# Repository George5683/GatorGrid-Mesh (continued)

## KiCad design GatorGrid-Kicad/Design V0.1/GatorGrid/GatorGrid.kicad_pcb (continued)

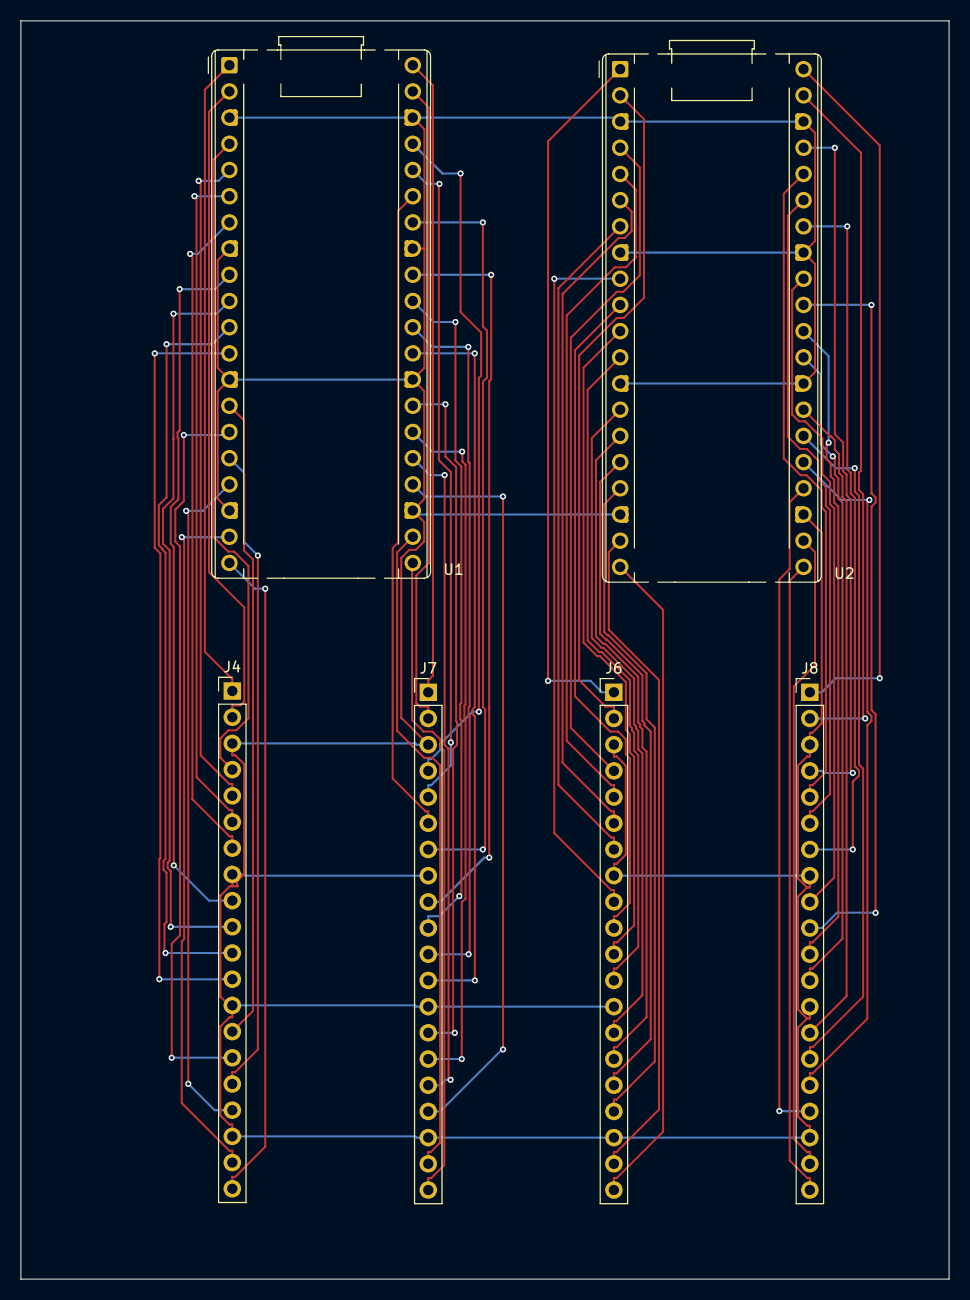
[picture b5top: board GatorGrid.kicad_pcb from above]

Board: 2 copper layers, 90.0 x 122.0 mm, 6 parts (0 on the bottom side), 65 nets.

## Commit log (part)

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2025-03-01 Working on the coding
2025-03-01 working on the coding...
2025-03-05 Fixed structure of project
2025-03-06 Restructured the code to have better functionality
2025-03-06 Restructured the code more
2025-03-06 added a comment
2025-03-06 removed testing commands
2025-03-07 Added STANode with scanning for other nodes *untested*
2025-03-07 Made multi-core polling and CMake for STA node testing
2025-03-10 converted the ap mode to have an enable/disable option for webpage generation
2025-03-10 implements doxygen with html
2025-03-11 testing...
2025-03-11 testing
2025-03-11 Add in the tcp client/server lib
2025-03-11 sta callback fix
2025-03-11 refactoring code and and added STANode tcp setup
2025-03-12 added tcp join message on init
2025-03-13 Add necessary TCP test functions to STA and AP libaries
2025-03-13 Fixed AP node TCP server test initalization
2025-03-13 refactor sta and ap mode setups to pull apart init code so they can be set up seperately themselves
2025-03-13 stash tcp branch
2025-03-13 Remove code that handles connection termination, also allows multiple clients to connect
2025-03-13 tcp client debugging
2025-03-13 Implements two way SPI communication
2025-03-13 working data transmission
2025-03-14 adding example files
2025-03-17 addded functionality
2025-03-19 Fixed memory leak issues and added sending a message for STA and receiving for AP
2025-03-23 updated README's
2025-03-25 Integrate Monocypher into code base
2025-03-27 Added picoNodeVectorClass
2025-04-01 Added a response back from AP whenever it gets a message
2025-04-01 Added messaging packets, INIT and DATA
2025-04-01 sets up automatic github pages workflow for doxygen
2025-04-01 Initial gh-pages commit
2025-04-01 Deploying to gh-pages from @ George5683/GatorGrid-Mesh@9408bfd56aad9ebf4bb832339b5d144ec4e8de41 🚀
2025-04-01 testing edits
2025-04-03 ACK messages
2025-04-03 updates index.html page for doxygen
2025-04-03 testing changes
2025-04-03 undo AP node accidental regression
2025-04-03 connection tracking vector
2025-04-03 Deploying to gh-pages from @ George5683/GatorGrid-Mesh@af39291f74b6d0666d905e82c10850361384b24b 🚀
2025-04-04 messages library and test TCP stream handling protocol
2025-04-05 unify RNGs
2025-04-07 Added sta functions and corresponding AP setup
2025-04-07 Updated APNode responding to incoming messages
2025-04-08 message recv methods
2025-04-08 fix AP control logic for parsing first message
2025-04-08 small fixes
2025-04-08 Add message storing Ring Buffer
2025-04-08 added a delay in Master SPI to wait for the Slave to initialize
2025-04-08 Integrate ring buffer into mesh node
2025-04-08 Rework server loop framework for AP node, now the main loop has been pulled outside of server specific functions
2025-04-08 Fix ring buffer
2025-04-08 Deploying to gh-pages from @ George5683/GatorGrid-Mesh@0fd86eadc9164e9a8be14ad41aa431bcd3f0da28 🚀
2025-04-08 fixing connection issues
2025-04-08 working connection
2025-04-08 tiny fixes
2025-04-08 Working yippee
2025-04-09 add src and dest to ring buffer, add ring buff digest logic to main
2025-04-09 Fix TCP packet buffering issue when doing message transfers
2025-04-09 Deploying to gh-pages from @ George5683/GatorGrid-Mesh@8590bb2787558b4fb964fe81840b6301445097a4 🚀
2025-04-09 added SPI to MESHNODE
2025-04-09 Deploying to gh-pages from @ George5683/GatorGrid-Mesh@9e40fa7865f5ab1c4f912dc9631bc267d9ae0b1f 🚀
2025-04-09 Changes to try to get everything to compile
2025-04-09 Testing merge between AP/STA and SPI
2025-04-09 Deploying to gh-pages from @ George5683/GatorGrid-Mesh@ebe74fe17888b8dbb08e9b242e9e568ddd66f5bc 🚀
2025-04-09 Deploying to gh-pages from @ George5683/GatorGrid-Mesh@3b9e1cfd1249049987f9cdc25aba9724e7d184a9 🚀
2025-04-09 STA Takes AP Node ID
2025-04-09 fixed bug for SPI sending ID
2025-04-09 Fix AP node crashing
2025-04-10 fixed pragma in source file
2025-04-10 Deploying to gh-pages from @ George5683/GatorGrid-Mesh@90d0fb41c1bd2f010006ecfe91de5703d05e04ad 🚀
2025-04-10 fixed ring buffer :)
2025-04-15 adds dht sensor library
2025-04-15 Creating tree for tracking nodes
2025-04-15 Update header
2025-04-17 spi and meshnode docs updated
2025-04-17 Deploying to gh-pages from @ George5683/GatorGrid-Mesh@56b9e9430297e3f74e8047001cf9007baed19d82 🚀
2025-04-17 spi docs
2025-04-17 Implementing inital tree for AP node
2025-04-17 Design update
2025-04-17 Deploying to gh-pages from @ George5683/GatorGrid-Mesh@2c9891114300862a98f139ec7ba850d3d9ad5e5b 🚀
2025-04-17 Deploying to gh-pages from @ George5683/GatorGrid-Mesh@6d5549e240390ef6749891b45eb29f188ea94038 🚀
2025-04-17 Deploying to gh-pages from @ George5683/GatorGrid-Mesh@1188b57ffe1db28e062e314415c503c34b555ade 🚀
2025-04-17 Deploying to gh-pages from @ George5683/GatorGrid-Mesh@081e60efe6d0598f2a8e630e937cc6f15b025ca3 🚀
2025-04-17 cpp file docs support
2025-04-17 fixed connection issues
2025-04-17 Deploying to gh-pages from @ George5683/GatorGrid-Mesh@b6e65119c27ab90f88d076bb01624436f59600d4 🚀
2025-04-17 updates spi docs
2025-04-17 comment out tree stuff, add more functionality for node id broadcasting
2025-04-17 Deploying to gh-pages from @ George5683/GatorGrid-Mesh@1f27188fee09cd10e11d067534907ece6cfc30a2 🚀
2025-04-17 sta fixes
2025-04-17 fix merge issue
2025-04-17 Deploying to gh-pages from @ George5683/GatorGrid-Mesh@30f25b66aed03688fc2cee9de35827c2699bc10d 🚀
2025-04-17 Deploying to gh-pages from @ George5683/GatorGrid-Mesh@1254ea3ee5fa6b1ab8e517cbe5d74b039ae0385c 🚀
2025-04-17 MPU Sensor Stuff
2025-04-17 Deploying to gh-pages from @ George5683/GatorGrid-Mesh@9b93db1a23dffa90aa3b0fb43b6147dcd9c644bb 🚀
2025-04-17 Deploying to gh-pages from @ George5683/GatorGrid-Mesh@03399c561fd94a97318b7014df2a12db13b2141b 🚀
2025-04-17 Update Doxyfile
2025-04-17 working doxygen
2025-04-17 ack message handling
2025-04-17 add get child count for update msg
2025-04-17 override bug fix
2025-04-17 comment out update message sending
2025-04-17 add voalitile
2025-04-17 hahahahahahha
2025-04-17 fixing ACK waiting
2025-04-17 added errors for NAK msg
2025-04-17 add extra nodes
2025-04-17 fix node 2
2025-04-17 ACK passing
2025-04-17 testing demo nodes
2025-04-17 make connect to root node
2025-04-18 refined Kicad
2025-04-18 add imu
2025-04-18 fixing
2025-04-18 most recent version
2025-04-18 meme
2025-04-18 Fix potential buffer wrap around issue
2025-04-18 AP fix rollback
2025-04-18 STA working sending message single way through root
2025-04-18 Fixes to Meshnode STA to ensure that it doesn't hang on one way message transfers
2025-04-18 Fixes for root
2025-04-21 Updated Readme instructions for DOxygen
2025-04-21 Unified STA send_data
2025-04-21 :facepalm:
2025-04-21 Mesh node send data
2025-04-22 doxy deploy
2025-04-22 Deploying to gh-pages from @ George5683/GatorGrid-Mesh@e9dace8dd1dc84a85a923d63efcd156fb2b5c584 🚀
2025-04-22 demo time
2025-04-22 Deploying to gh-pages from @ George5683/GatorGrid-Mesh@c808830c7483f19a16e4caf8c3fb4dd0ef240578 🚀
2025-04-25 fixing errors
2025-08-04 added files for voltage booster
2025-08-13 updated the schematic to have no errors on the error check
2025-08-21 updated PCB
2025-08-27 added V2
2025-08-28 Updated power management, channel usage and wpa protection for consistency testing
2025-08-28 Updating Kicad
2025-08-28 added cmake for SPI testing
2025-08-29 Added wire tests
2025-08-29 Updated SPI
2025-09-02 fixed connections
2025-09-04 Minor changes to schematic
2025-09-04 Update MeshNodeAP.cpp for new SPI
2025-09-04 Update MeshNodeSTA.cpp for SPI
2025-09-04 Update MeshNode.hpp to include SPI stuff
2025-09-04 updating the bugs
    Removed mention of SPI delay in README.
2025-09-04 Added test_tree files
2025-09-11 Create SerialMessages
2025-09-16 handling serial msgs
2025-09-16 Added UART Library :D
2025-09-16 Working commit
2025-09-17 added children tree get chidren and reverted CMakeLists
2025-09-17 added doxygen comments to APNode functions
2025-09-17 fixing KICAD
2025-09-18 reworked cmakelists, you are welcome lol
2025-09-18 cleaned up header and removed unused variables
2025-09-18 removed dynamic allocation from parseMessage
2025-09-18 Hype tree stuff with aura and hype moments
2025-09-18 Update MeshNodeAP.cpp
    set power mode to performance rather then defualt
2025-09-18 Update MeshNodeSTA.cpp
    fix connection issue for STA
2025-09-23 adding a Version 3.0
2025-09-23 Added Kicad to the readme features section
2025-09-23 Fixing Readme's
2025-09-24 working on it
2025-09-25 flushing out send_msg
2025-09-25 Added RSSI testing hype moment
2025-09-25 Completely removed parseMessage and dynamic allocation
2025-09-25 AP inter-node message handling *needs testing*
2025-09-26 Finalized V3.0
2025-09-30 unification work
2025-10-01 Cole unified (#21)
    * unify uart
    * unification work
2025-10-01 Ggm 1 (#18)
    * cleaned up header and removed unused variables
    * removed dynamic allocation from parseMessage
    * flushing out send_msg
    * Completely removed parseMessage and dynamic allocation
    * AP inter-node message handling *needs testing*
    * fixed find_path_parent and split STANodes files
2025-10-01 removed commented out code
2025-10-01 tested serial and updating tree fixes
2025-10-01 Finished V3
2025-10-01 Moving things
2025-10-02 Serial buf and UART fixes
2025-10-02 fixed double isr with toggle, fix is TEMPORARY, we need to look into dma https://github.com/rossihwang/pico_dma_uart
2025-10-02 UART sync issue fix
2025-10-02 comment ring buffer
2025-10-02 comment and sanity check uart
2025-10-03 resizing messages
2025-10-03 fix sta ap sync over UART
2025-10-03 got uart working again
2025-10-03 Demo updates, still seeing ISR issues UPDATE messages are being sent properly
2025-10-05 Fix buffer size to save space
2025-10-05 Working DHT11 library
2025-10-05 tree serializer
2025-10-05 more demo progress
2025-10-06 adds tree gui command
2025-10-06 starting force update tree operations
2025-10-06 Demo (#26)
    * resizing messages
    * fix sta ap sync over UART
    * got uart working again
    * more demo fixes
    * Demo updates, still seeing ISR issues UPDATE messages are being sent properly
    * Fix buffer size to save space
2025-10-06 Merge assist (#28)
    * Updated power management, channel usage and wpa protection for consistency testing
    * added comments
    * added comments
    * added cmake for SPI testing
    * Added wire tests
    * Updated SPI
2025-10-06 Deploying to gh-pages from @ George5683/GatorGrid-Mesh@56c468103457720996b03cda07a3b77214f6505f 🚀
2025-10-14 Finished updating V4.0 schematic
2025-10-16 final demo fixes
2025-10-16 Demo fixes (#30)
    * added 3rd node
    * final demo fixes
2025-10-16 Merge fixes (#31)
    * added 3rd node
    * merge fixes
2025-10-21 Moved around some components in the PCB
2025-10-21 removes zone identifier files (#32)
2025-10-21 removes zis and updates git ingnore
2025-10-21 removes zis and updates git ingnore (#33)
2025-10-23 Added a root check for the self heal. Also made the nodes actually connect
2025-10-23 Added default return in self-healing
2025-10-23 added link status check
2025-10-23 Added root checks and handling to self-healing
2025-10-23 calls children tree function
2025-10-29 adds return statement
2025-10-29 freeing on error
2025-10-30 Added more self healing functions, specifically child ping message
2025-10-30 f my chungus life, reconnect on error not working
2025-10-30 More self healing stuff
2025-10-30 Fully implemented selfhealing from a signal side
2025-10-30 moves node in children tree
2025-10-31 working reconnection on AP failure
2025-11-02 Kicad Final merge (#36)
    * Finished updating V4.0 schematic
    * Finished PCB design for V4.0
    * Moved around some components in the PCB
    * Finihsed design
2025-11-02 fix stuffz
2025-11-02 fix ignore
2025-11-02 brah
2025-11-02 removed ap link status check
2025-11-06 Removed the parent check, orphans become Batman
2025-11-06 self healing fix for children tree
2025-11-06 Added extra scan
2025-11-13 added tictactoe class
2025-11-13 ttt set up on sta 2
2025-11-15 demo testing
2025-11-15 working ttt on 1 and 2
2025-11-18 added debug statements
2025-11-18 fixed mutual connection issues
2025-11-18 blacklist fix
2025-11-19 further ttt edits
2025-11-19 fixes on ttt
2025-11-19 correcting sta 1
2025-11-20 add nodes 4 and 5 to cmake
2025-11-20 fix nodes 4 and 5
2025-11-20 demo root showing wins
2025-11-20 fixing sta_root crash
2025-11-20 fix format string
